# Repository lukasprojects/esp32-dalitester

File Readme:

# ESP32 DALI Tester (TFT UI + Encoder + Bus Monitor)

A compact, hands-on DALI tool built around an ESP32 with a 2.2" ILI9341 TFT and a rotary encoder. It can send DALI commands, scan devices, commission / change short addresses, 
clone key configuration values, reset device config, and monitor bus traffic.

> Note on provenance:  
> The firmware was created using AI-assisted “vibe coding” (with human iteration and testing).  
> The PCB / hardware wiring & integration were designed and built by hand.
> Current FW version (1.3.8) only allows for DALI1 and a few DALI2 devices (not all sensors are found).
> Please understand that the DALI bus may not be isolated from mains voltage! Do not use the internal power supply if there is allready voltage on the bus!
  If you are using the internal power supply, the DALI bus is not fully isolated! If you use an external supply, the tool is fully isolated.
  The internal power supply should be able to output 150mA, so it is not capable to supply a whole set of 64 devices, i tested it with more than 10 devices.

---

# Features

- TFT UI (ILI9341, 320×240) with header/footer and a scrollable home menu
- Rotary encoder navigation
  - Rotate: navigate lists / change values
  - Short click: select / execute
  - Long press (≥ 700 ms): back
  - Looong press (≥ 8000 ms): easteregg
- DALI Master (via `qqqlab/DALI-Lighting-Interface` / `qqqDALI`)
  - Send common commands (ON/OFF/MIN/MAX)
  - Query status, levels, device type
- Commissioning / addressing
  - Commission all devices
  - Commission unaddressed devices
  - Change short address (initialize → program → verify → terminate)
- Clone configuration
  - Capture and apply: max/min level, power-on level, system-failure level, fade time, fade rate
- Reset config (treats NO_REPLY as success, useful for some drivers)
- Bus Monitor
  - Displays decoded forward frames (address+data) and backward replies
  - Live mode + freeze/scroll mode

---

# Hardware

Core components
- ESP32 (DevKit style)
- ILI9341 2.2" SPI TFT (Adafruit compatible)
- Rotary encoder with push button
- DALI interface hardware (tested with Waveshare Pico-DALI2 and a Tridonic DALI USB “mouse” for generating traffic)
                           
---

# Firmware / Libraries

- Arduino framework on ESP32
- Display:
  - `Adafruit_GFX`
  - `Adafruit_ILI9341`
- DALI:
  - `qqqlab/DALI-Lighting-Interface` (`qqqDALI`)

The DALI timing is driven by a periodic ESP32 hardware timer ISR calling `dali.timer()`.

---

# Building

PlatformIO
1. Install VS Code + PlatformIO
2. Clone this repository
3. Open the folder in VS Code
4. Build and upload:
   - `PlatformIO: Build`
   - `PlatformIO: Upload`
5. Monitor serial output:
   - `PlatformIO: Monitor` (115200 baud)

---

# Project Status

This is an actively iterated DIY project. Expect occasional breaking changes while improving UI, decoding, or hardware compatibility.

---

# Contributing

Issues and PRs are welcome — especially for:
- Additional command decoding in the bus monitor
- Compatibility notes for more DALI interface boards
- UI improvements without increasing RAM usage

---

# License

Please check the repository for the license file(s).  
This project depends on third-party libraries which come with their own licenses (notably the `qqqDALI` library).

---

# Credits

- `qqqlab/DALI-Lighting-Interface` (`qqqDALI`) for the DALI stack
- Adafruit GFX + ILI9341 libraries for the display layer

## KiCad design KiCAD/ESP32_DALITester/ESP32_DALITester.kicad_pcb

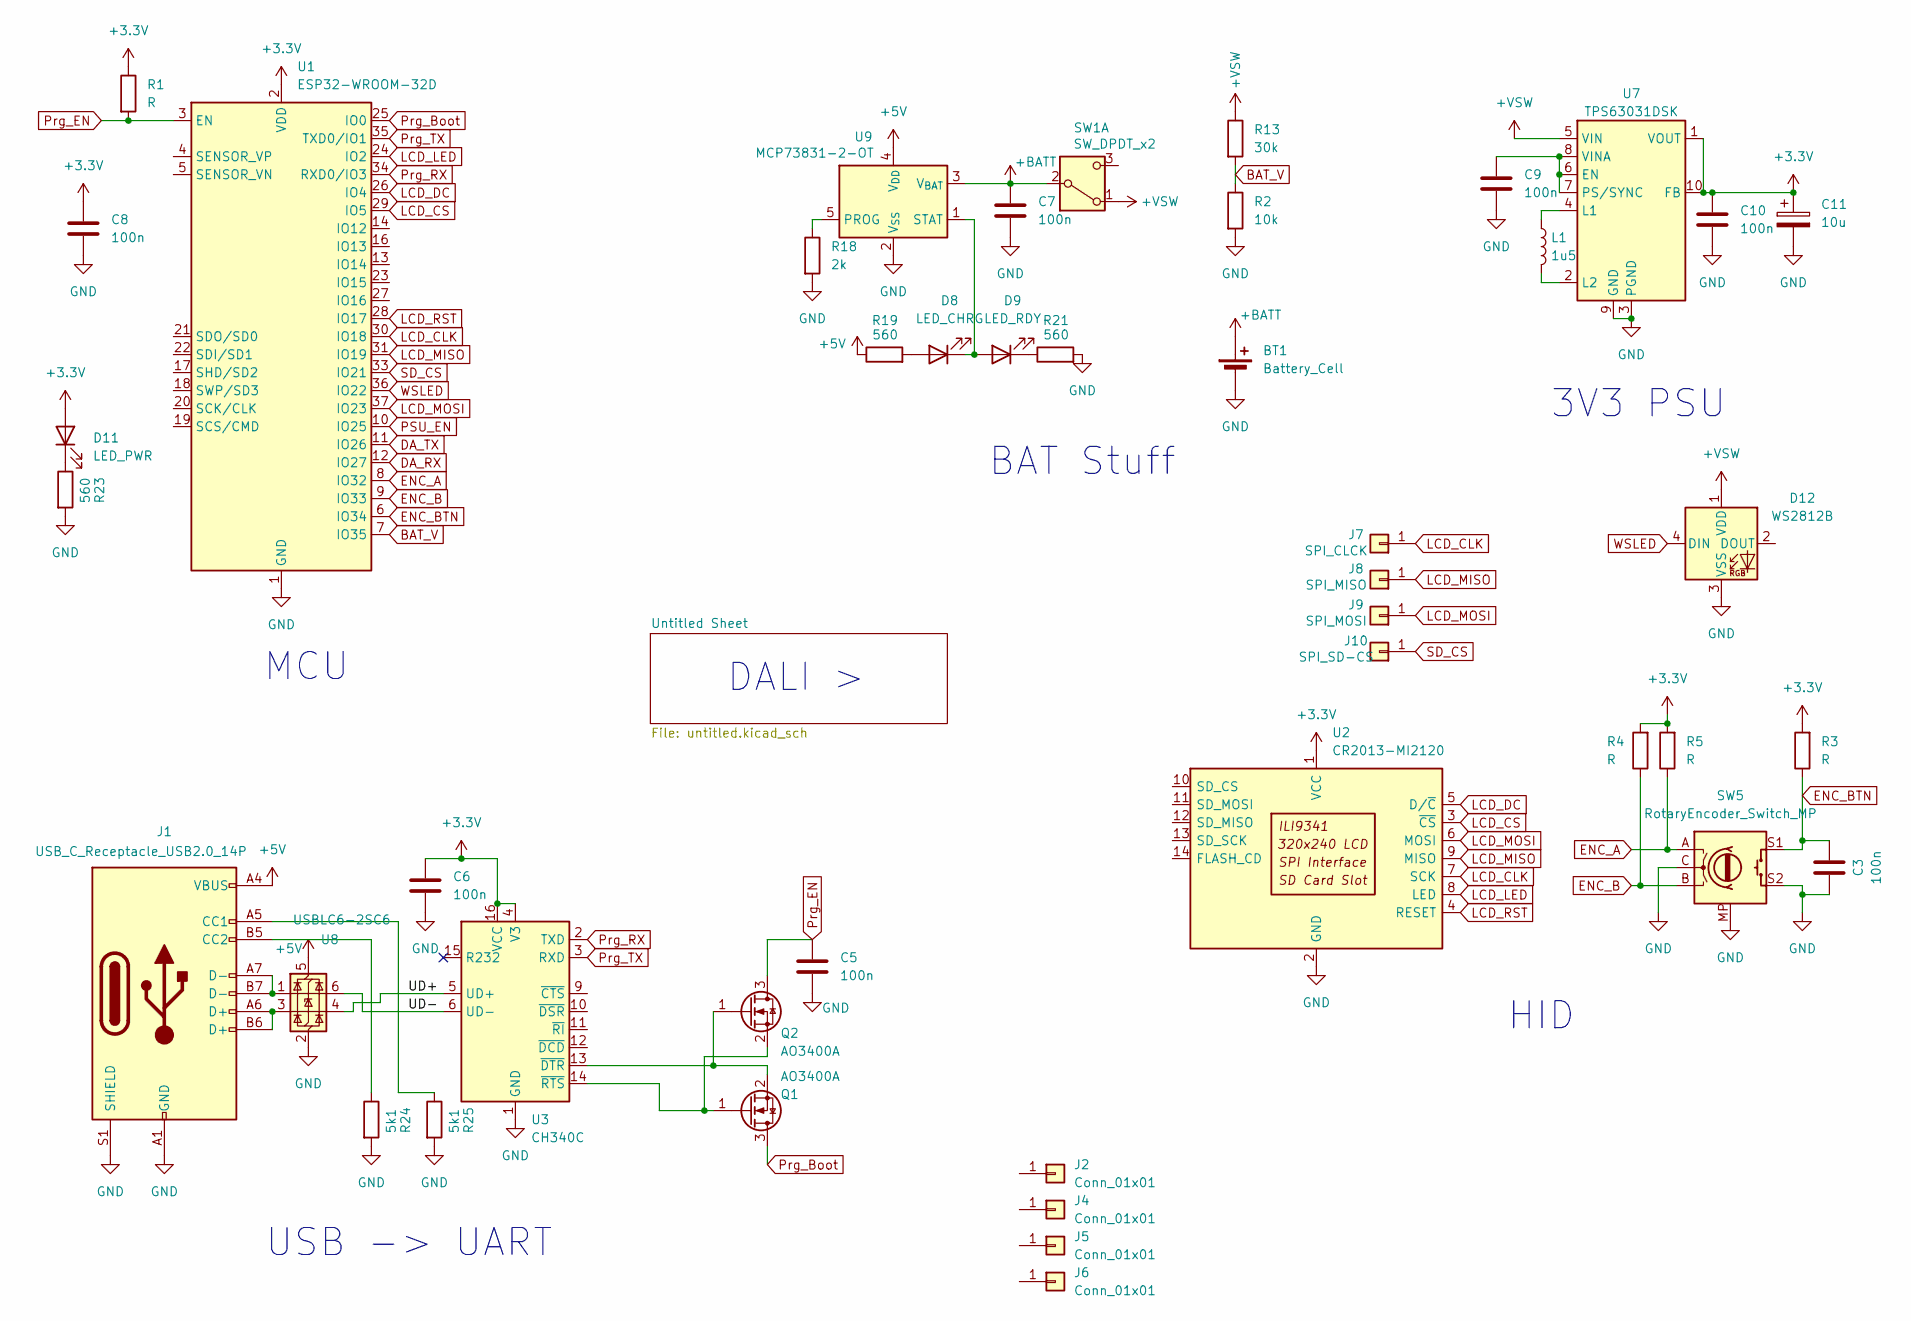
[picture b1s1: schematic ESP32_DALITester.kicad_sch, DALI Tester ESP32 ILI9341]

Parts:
BT1: Battery_Cell; JST_PH_S2B-PH-SM4-TB_1x02-1MP_P2.00mm_Horizontal
C3, C5, C6, C7, C8, C9, C10: 100n; C_0603_1608Metric_Pad1.08x0.95mm_HandSolder
C11: 10u; CP_Elec_6.3x3
D8: LED_CHRG; LED_0603_1608Metric_Pad1.05x0.95mm_HandSolder
D9: LED_RDY; LED_0603_1608Metric_Pad1.05x0.95mm_HandSolder
D11: LED_PWR; LED_0603_1608Metric_Pad1.05x0.95mm_HandSolder
D12: WS2812B; LED_WS2812B_PLCC4_5.0x5.0mm_P3.2mm
J1: USB_C_Receptacle_USB2.0_14P; USB_C_Receptacle_G-Switch_GT-USB-7010ASV
J2, J4, J5, J6: Conn_01x01; MountingHole_3mm
J7: SPI_CLCK; SolderWirePad_1x01_SMD_1x2mm
J8: SPI_MISO; SolderWirePad_1x01_SMD_1x2mm
J9: SPI_MOSI; SolderWirePad_1x01_SMD_1x2mm
J10: SPI_SD-CS; SolderWirePad_1x01_SMD_1x2mm
L1: 1u5; L_APV_APH0420
Q1, Q2: AO3400A; SOT-23
R1, R3, R4, R5: R; R_0603_1608Metric_Pad0.98x0.95mm_HandSolder
R2: 10k; R_0603_1608Metric_Pad0.98x0.95mm_HandSolder
R13: 30k; R_0603_1608Metric_Pad0.98x0.95mm_HandSolder
R18: 2k; R_0603_1608Metric_Pad0.98x0.95mm_HandSolder
R19, R21, R23: 560; R_0603_1608Metric_Pad0.98x0.95mm_HandSolder
R24, R25: 5k1; R_0603_1608Metric_Pad0.98x0.95mm_HandSolder
SW1: SW_DPDT_x2; SW_Slide_SPDT_Angled_CK_OS102011MA1Q
SW5: RotaryEncoder_Switch_MP; BOURNS PEC11J-9220F-H0015
U1: ESP32-WROOM-32D
U2: CR2013-MI2120
U3: CH340C; SOIC-16_3.9x9.9mm_P1.27mm
U7: TPS63031DSK; WSON-10-1EP_2.5x2.5mm_P0.5mm_EP1.2x2mm
U8: USBLC6-2SC6; SOT-23-6
U9: MCP73831-2-OT; SOT-23-5

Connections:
+3.3V: C6.1, C8.1, C10.1, C11.1, D11.2 (A), R1.1, R3.2, R4.2, R5.2, U1.2 (VDD), U2.1 (VCC), U3.4 (V3), U3.16 (VCC), U7.1 (VOUT), U7.10 (FB); also elsewhere on the board
+5V: J1.A4 (VBUS), J1.A9 (VBUS), J1.B4 (VBUS), J1.B9 (VBUS), R19.1, U8.5 (VBUS), U9.4 (V_{DD})
+BATT: BT1.2 (+), C7.1, SW1.2 (B), U9.3 (V_{BAT})
+VSW: D12.1 (VDD), R13.1, SW1.1 (A), U7.5 (VIN); also elsewhere on the board
/UD+: U3.5 (UD+), U8.4 (I/O2)
/UD-: U3.6 (UD-), U8.6 (I/O1)
BAT_V: R2.1, R13.2, U1.7 (IO35)
DA_RX: U1.12 (IO27); also elsewhere on the board
DA_TX: U1.11 (IO26); also elsewhere on the board
ENC_A: R5.1, SW5.A, U1.8 (IO32)
ENC_B: R4.1, SW5.B, U1.9 (IO33)
ENC_BTN: C3.2, R3.1, SW5.S1, U1.6 (IO34)
GND: BT1.1 (-), C3.1, C5.2, C6.2, C7.2, C8.2, C9.2, C10.2, C11.2, D12.3 (VSS), J1.A1 (GND), J1.A12 (GND), J1.B1 (GND), J1.B12 (GND), J1.S1 (SHIELD), R2.2, R18.2, R21.2, R23.2, R24.2, R25.2, SW5.C, SW5.MP, SW5.S2, U1.1 (GND), U1.15 (GND), U1.38 (GND), U1.39 (GND), U2.2 (GND), U3.1 (GND), U7.3 (PGND), U7.9 (GND), U7.11 (PGND), U8.2 (GND), U9.2 (V_{SS}); also elsewhere on the board
LCD_CLK: J7.1, U1.30 (IO18), U2.7 (SCK)
LCD_CS: U1.29 (IO5), U2.3 (~CS)
LCD_DC: U1.26 (IO4), U2.5 (D/~C)
LCD_LED: U1.24 (IO2), U2.8 (LED)
LCD_MISO: J8.1, U1.31 (IO19), U2.9 (MISO)
LCD_MOSI: J9.1, U1.37 (IO23), U2.6 (MOSI)
LCD_RST: U1.28 (IO17), U2.4 (RESET)
unnamed: D8.2 (A), R19.2
unnamed: D8.1 (K), D9.2 (A), U9.1 (STAT)
unnamed: D9.1 (K), R21.1
unnamed: D11.1 (K), R23.1
unnamed: J1.A5 (CC1), R25.1
unnamed: J1.B5 (CC2), R24.1
unnamed: J1.A6 (D+), J1.B6 (D+), U8.3 (I/O2)
unnamed: J1.A7 (D-), J1.B7 (D-), U8.1 (I/O1)
unnamed: Q1.1 (G), Q2.2 (S), U3.14 (~RTS)
unnamed: Q1.2 (S), Q2.1 (G), U3.13 (~DTR)
unnamed: C9.1, U7.6 (EN), U7.7 (PS/SYNC), U7.8 (VINA)
unnamed: L1.1, U7.4 (L1)
unnamed: L1.2, U7.2 (L2)
unnamed: R18.1, U9.5 (PROG)
PSU_EN: U1.10 (IO25); also elsewhere on the board
Prg_Boot: Q1.3 (D), U1.25 (IO0)
Prg_EN: C5.1, Q2.3 (D), R1.2, U1.3 (EN)
Prg_RX: U1.34 (RXD0/IO3), U3.2 (TXD)
Prg_TX: U1.35 (TXD0/IO1), U3.3 (RXD)
SD_CS: J10.1, U1.33 (IO21)
WSLED: D12.4 (DIN), U1.36 (IO22)

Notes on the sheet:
DALI >
HID
3V3 PSU
BAT Stuff
USB -> UART
MCU

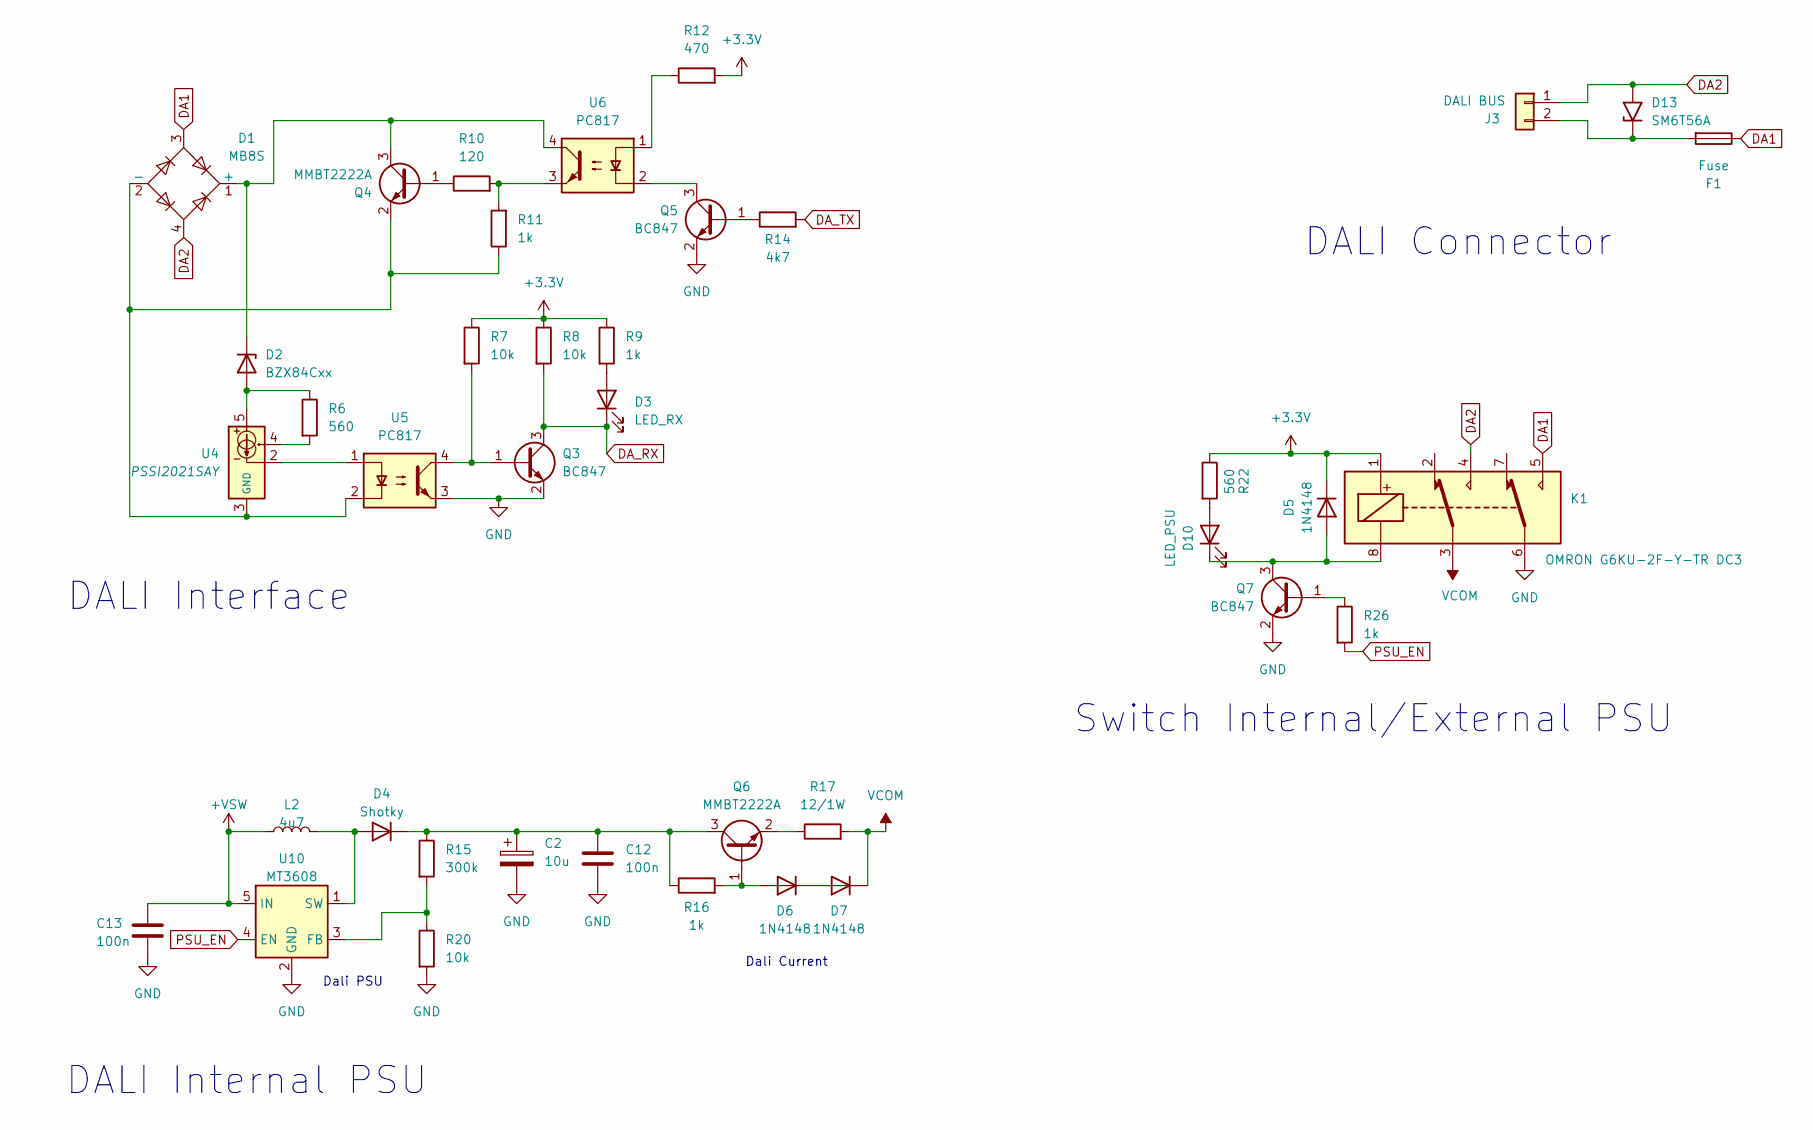
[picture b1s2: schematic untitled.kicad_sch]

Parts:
C2: 10u; CP_Elec_6.3x3
C12, C13: 100n; C_0603_1608Metric_Pad1.08x0.95mm_HandSolder
D1: MB8S; OnSemi_751EP_SOIC-4_3.9x4.725mm_P2.54mm
D2: BZX84Cxx; SOT-23
D3: LED_RX; LED_0603_1608Metric_Pad1.05x0.95mm_HandSolder
D4: Shotky; D_SOD-123
D5, D6, D7: 1N4148; D_SOD-123
D10: LED_PSU; LED_0603_1608Metric_Pad1.05x0.95mm_HandSolder
D13: SM6T56A; D_SMB
F1: Fuse; Fuse_1206_3216Metric_Pad1.42x1.75mm_HandSolder
J3: DALI BUS; PhoenixContact_MC_1,5_2-G-3.5_1x02_P3.50mm_Horizontal
K1: OMRON G6KU-2F-Y-TR DC3
L2: 4u7; L_APV_APH0420
Q3, Q5, Q7: BC847; SOT-23
Q4, Q6: MMBT2222A; SOT-23
R6, R22: 560; R_0603_1608Metric_Pad0.98x0.95mm_HandSolder
R7, R8, R20: 10k; R_0603_1608Metric_Pad0.98x0.95mm_HandSolder
R9, R11, R16, R26: 1k; R_0603_1608Metric_Pad0.98x0.95mm_HandSolder
R10: 120; R_0603_1608Metric_Pad0.98x0.95mm_HandSolder
R12: 470; R_0603_1608Metric_Pad0.98x0.95mm_HandSolder
R14: 4k7; R_0603_1608Metric_Pad0.98x0.95mm_HandSolder
R15: 300k; R_0603_1608Metric_Pad0.98x0.95mm_HandSolder
R17: 12/1W; R_1206_3216Metric_Pad1.30x1.75mm_HandSolder
U4: PSSI2021SAY; SOT-353_SC-70-5
U5, U6: PC817; SMDIP-4_W7.62mm
U10: MT3608; SOT-23-6

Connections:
+3.3V: D5.1 (K), K1.1, R7.1, R8.1, R9.1, R12.2, R22.1; also elsewhere on the board
+VSW: C13.1, L2.1, U10.5 (IN); also elsewhere on the board
DA1: D1.3, F1.1, K1.5
DA2: D1.4, D13.2 (A2), J3.1, K1.4
DA_RX: D3.1 (K), Q3.3 (C), R8.2; also elsewhere on the board
DA_TX: R14.2; also elsewhere on the board
GND: C2.2, C12.2, C13.2, K1.6, Q3.2 (E), Q5.2 (E), Q7.2 (E), R20.2, U5.3, U10.2 (GND); also elsewhere on the board
unnamed: D1.1 (+), D2.3 (K), Q4.3 (C), U6.4
unnamed: D1.2 (-), Q4.2 (E), R11.1, U4.3 (GND), U5.2
unnamed: D2.1 (A), R6.1, U4.5
unnamed: D3.2 (A), R9.2
unnamed: D4.2 (A), L2.2, U10.1 (SW)
unnamed: C2.1, C12.1, D4.1 (K), Q6.3 (C), R15.1, R16.1
unnamed: D6.2 (A), Q6.1 (B), R16.2
unnamed: D6.1 (K), D7.2 (A)
unnamed: D10.2 (A), R22.2
unnamed: D5.2 (A), D10.1 (K), K1.8, Q7.3 (C)
unnamed: D13.1 (A1), F1.2, J3.2
unnamed: Q3.1 (B), R7.2, U5.4
unnamed: Q4.1 (B), R10.1
unnamed: Q5.1 (B), R14.1
unnamed: Q5.3 (C), U6.2
unnamed: Q6.2 (E), R17.1
unnamed: Q7.1 (B), R26.1
unnamed: R6.2, U4.4
unnamed: R10.2, R11.2, U6.3
unnamed: R12.1, U6.1
unnamed: U4.2, U5.1
unnamed: R15.2, R20.1, U10.3 (FB)
PSU_EN: R26.2, U10.4 (EN); also elsewhere on the board
VCOM: D7.1 (K), K1.3, R17.2

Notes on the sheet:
Dali Current
DALI Connector
DALI Interface
DALI Internal PSU
Switch Internal/External PSU
Dali PSU

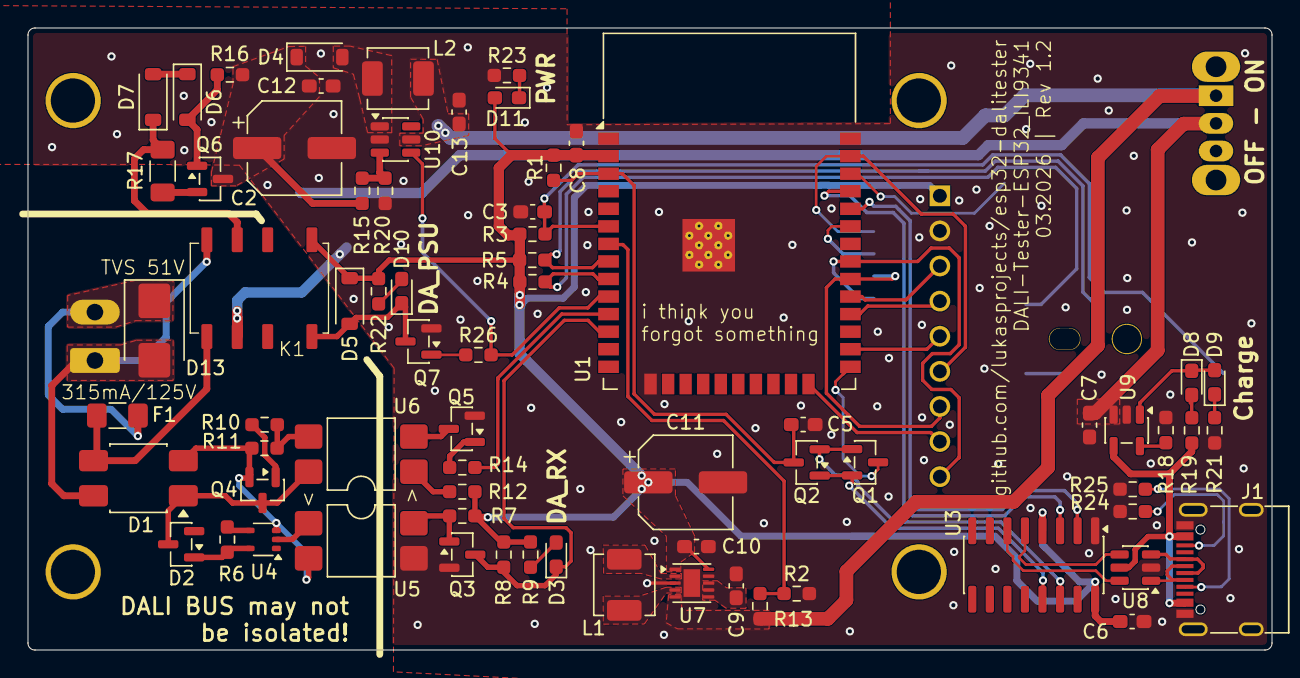
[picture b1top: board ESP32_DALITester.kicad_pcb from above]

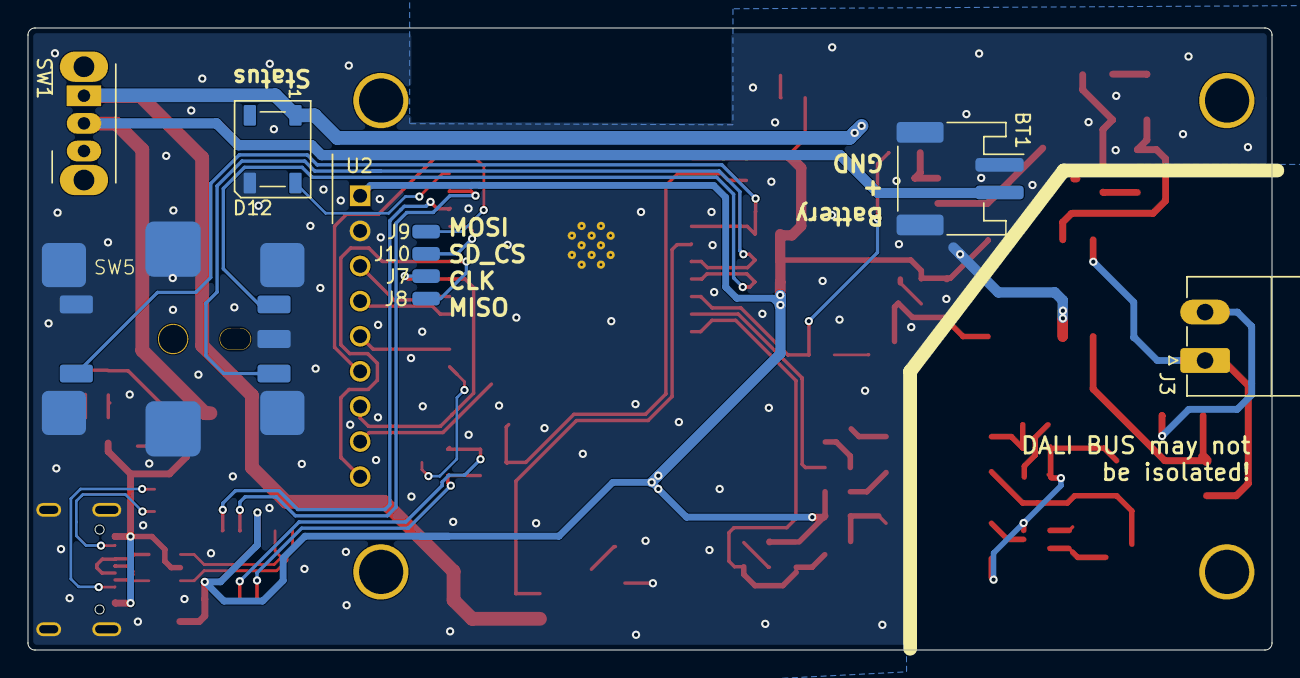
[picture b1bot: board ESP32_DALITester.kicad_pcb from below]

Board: 2 copper layers, 90.0 x 45.0 mm, 84 parts (10 on the bottom side), 66 nets.

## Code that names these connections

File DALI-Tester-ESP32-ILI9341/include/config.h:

/**
 * @file config.h
 * @brief Hardware pin configuration and settings for DALI Tester
 * 
 * Modify these defines to match your hardware setup.
 */

#ifndef CONFIG_H
#define CONFIG_H

// =============================================================================
// Firmware Version
// =============================================================================
#define FW_VERSION  "1.4.5"
#define HW_VERSION  "1.2"

// =============================================================================
// TFT Display Configuration (ILI9341 2.8" SPI)
// =============================================================================
#define TFT_CS      5           // Chip Select
#define TFT_DC      4           // Data/Command
#define TFT_RST     17          // Reset (-1 if connected to ESP32 EN/RST)
#define TFT_MOSI    23          // SPI MOSI (default ESP32 VSPI)
#define TFT_SCLK    18          // SPI SCLK (default ESP32 VSPI)
#define TFT_MISO    19          // SPI MISO (optional for touch)
#define TFT_LED     2           // Backlight control (HIGH = on)

// Display settings
#define TFT_WIDTH   320
#define TFT_HEIGHT  240
#define TFT_ROTATION 1      // Landscape mode

// =============================================================================
// Rotary Encoder Configuration
// =============================================================================
#define ENC_A       33      // Encoder A signal
#define ENC_B       32      // Encoder B signal
#define ENC_BTN     34      // Encoder push button (active LOW with external pullup)

#define ENCODER_DIR     -1   // Direction: +1 or -1 to reverse
#define ENC_STEP_DIV    4   // Steps per detent (typical: 4 for most encoders)

// Button timing
#define BTN_DEBOUNCE_MS     50      // Debounce time in ms
#define LONG_PRESS_MS       700     // Long press threshold in ms

// =============================================================================
// DALI Interface Configuration
// =============================================================================
#define DALI_TX     26      // DALI transmit pin
#define DALI_RX     27      // DALI receive pin

// TX/RX inversion settings (depends on your optocoupler/transistor circuit)
// For Waveshare Pico-DALI2: Try both polarities if one doesn't work
#define DALI_TX_INVERT  true    // true = TX HIGH pulls bus LOW (matches working reference firmware)
#define DALI_RX_INVERT  false   // false for Waveshare Pico-DALI2

// =============================================================================
// DALI PSU Control
// =============================================================================
#define DALI_PSU_EN         25      // PSU enable pin
#define PSU_EN_ACTIVE_HIGH  true    // true if HIGH enables PSU

// =============================================================================
// UI Configuration
// =============================================================================
#define HEADER_HEIGHT       32      // Header bar height in pixels (larger for better badge visibility)
#define FOOTER_HEIGHT       20      // Footer bar height in pixels
#define CONTENT_TEXT_SIZE   2       // Text size for content area (1=6x8, 2=12x16)
#define MENU_ITEM_HEIGHT    24      // Height per menu item (adjust for text size)

// Colors (RGB565)
#define COLOR_BG            0x0000  // Black background
#define COLOR_TEXT          0xFFFF  // White text
#define COLOR_HEADER_BG     0x001F  // Blue header
#define COLOR_FOOTER_BG     0x0010  // Dark blue footer
#define COLOR_PROJECT_HEADER_BG 0xA800  // Dark red header in loaded project mode
#define COLOR_PROJECT_FOOTER_BG 0x5800  // Dark red footer in loaded project mode
#define COLOR_HIGHLIGHT     0x07E0  // Green highlight
#define COLOR_SELECTED      0x07FF  // Cyan selection
#define COLOR_WARNING       0xFBE0  // Orange warning
#define COLOR_ERROR         0xF800  // Red error
#define COLOR_SUCCESS       0x07E0  // Green success
#define COLOR_BADGE_IDLE    0x4208  // Gray badge
#define COLOR_BADGE_ACT     0x07E0  // Green - activity
#define COLOR_BADGE_SEND    0xFFE0  // Yellow - sending
#define COLOR_BADGE_ERR     0xF800  // Red - error

// =============================================================================
// Bus Monitor Configuration
// =============================================================================
#define BUSMON_MAX_ENTRIES  80      // Ring buffer size for bus monitor
#define BUSMON_REFRESH_MS   80      // Max refresh rate (~12fps)

// =============================================================================
// Locate Function
// =============================================================================
#define LOCATE_INTERVAL_MIN     200     // Minimum interval in ms
#define LOCATE_INTERVAL_MAX     3000    // Maximum interval in ms
#define LOCATE_INTERVAL_STEP    100     // Step size in ms
#define LOCATE_INTERVAL_DEFAULT 1000     // Default interval

// =============================================================================
// DALI Timing
// =============================================================================
#define DALI_TIMER_US   104     // Timer interrupt interval in microseconds

// =============================================================================
// Battery Monitoring (1S LiPo)
// =============================================================================
#define BATTERY_ADC_PIN     35      // GPIO 35 (ADC1_CH7, Input only)

// Voltage divider: Connect battery through voltage divider to this pin
// For 1S LiPo (4.2V max): Use 2:1 divider (e.g., 100k + 100k)
//   Battery+ ---[100k]---+---[100k]--- GND
//                        |
//                     GPIO 34
//
// Calibration values (adjust based on your resistors)
#define BATTERY_DIVIDER_RATIO   2.0     // Voltage divider ratio (R1+R2)/R2
#define BATTERY_VOLT_MIN        3.0     // Empty battery voltage (0%)
#define BATTERY_VOLT_MAX        4.2     // Full battery voltage (100%)
#define BATTERY_READ_INTERVAL   5000    // Read interval in ms
#define BATTERY_ADC_SAMPLES     16      // Number of samples to average

// ADC calibration (ESP32 ADC can be non-linear, adjust if needed)
#define BATTERY_ADC_VREF        3.3     // ADC reference voltage (with 11dB attenuation)

// =============================================================================
// SD Card Configuration
// =============================================================================
// Default setup shares the TFT SPI bus and uses a separate CS pin.
// Adjust these pins to match your SD card wiring.
#define SD_CS               21
#define SD_SPI_SCLK         TFT_SCLK
#define SD_SPI_MISO         TFT_MISO
#define SD_SPI_MOSI         TFT_MOSI

#endif // CONFIG_H

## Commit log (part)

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2026-02-25 Initial README for ESP32 DALI Tester project
    Add detailed project description, features, hardware, and usage instructions for the ESP32 DALI Tester.
2026-04-19 Delete KiCAD/ESP32_DALITester directory
    Old Version
2026-04-19 Add files via upload
    Rev1.2, tested and working, but DALI voltage around 15V
2026-04-19 Add files via upload
    Rev1_2 Gerber, bugfixes at DALI powersupply
2026-04-19 Update Readme
    deAIfy the text
2026-04-19 Add files via upload
    PCB Renders
2026-04-19 Add files via upload
    FW_1.3.8
2026-04-19 Update Readme
    typos
